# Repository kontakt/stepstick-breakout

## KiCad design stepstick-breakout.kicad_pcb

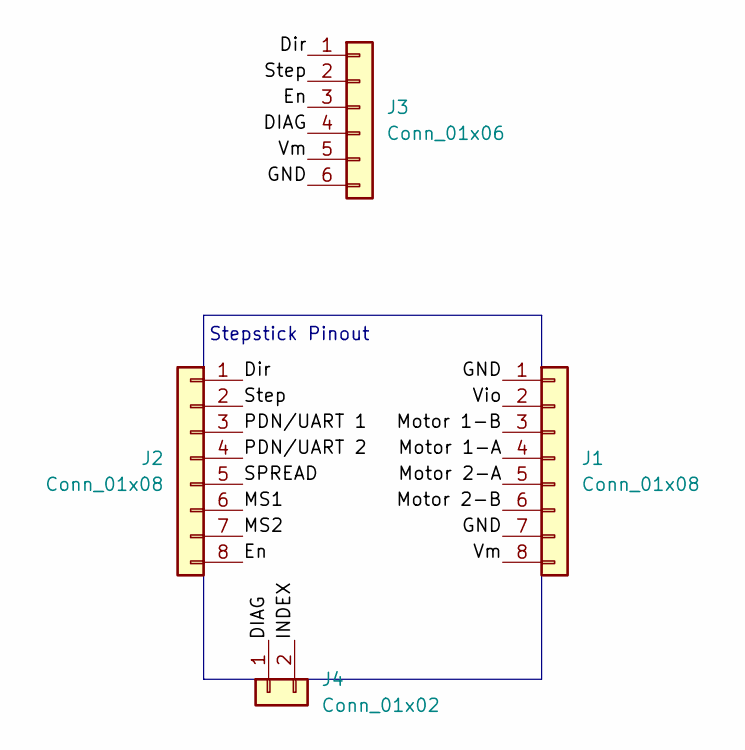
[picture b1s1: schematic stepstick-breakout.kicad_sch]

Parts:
J1, J2: Conn_01x08; PinHeader_1x08_P2.54mm_Vertical
J3: Conn_01x06; JST_XH_B6B-XH-A_1x06_P2.50mm_Vertical
J4: Conn_01x02; PinHeader_1x02_P2.54mm_Vertical

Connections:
/DIAG: J3.4, J4.1
/Dir: J2.1, J3.1
/En: J2.8, J3.3
/GND: J1.1, J1.7, J3.6
/INDEX: J4.2
/MS1: J2.6
/MS2: J2.7
/Motor 1-A: J1.4
/Motor 1-B: J1.3
/Motor 2-A: J1.5
/Motor 2-B: J1.6
/PDN/UART 1: J2.3
/PDN/UART 2: J2.4
/SPREAD: J2.5
/Step: J2.2, J3.2
/Vio: J1.2
/Vm: J1.8, J3.5

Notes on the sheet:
Stepstick Pinout

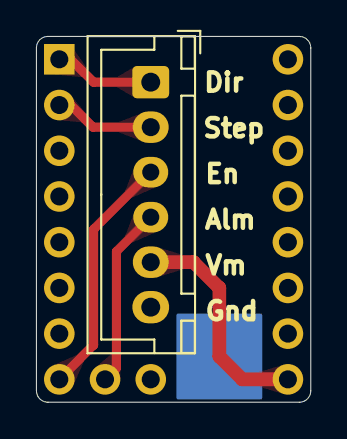
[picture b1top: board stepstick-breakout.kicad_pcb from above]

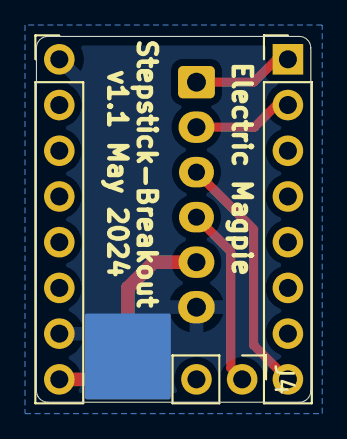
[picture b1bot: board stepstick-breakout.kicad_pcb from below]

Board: 2 copper layers, 15.2 x 20.3 mm, 4 parts (3 on the bottom side), 6 nets.

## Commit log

2024-05-20 Rev 1.0
    First Batch
2024-05-20 v1.1
    Widened JST-XH mounting holes to theoretically support a 2.54mm pitch screw terminal array
